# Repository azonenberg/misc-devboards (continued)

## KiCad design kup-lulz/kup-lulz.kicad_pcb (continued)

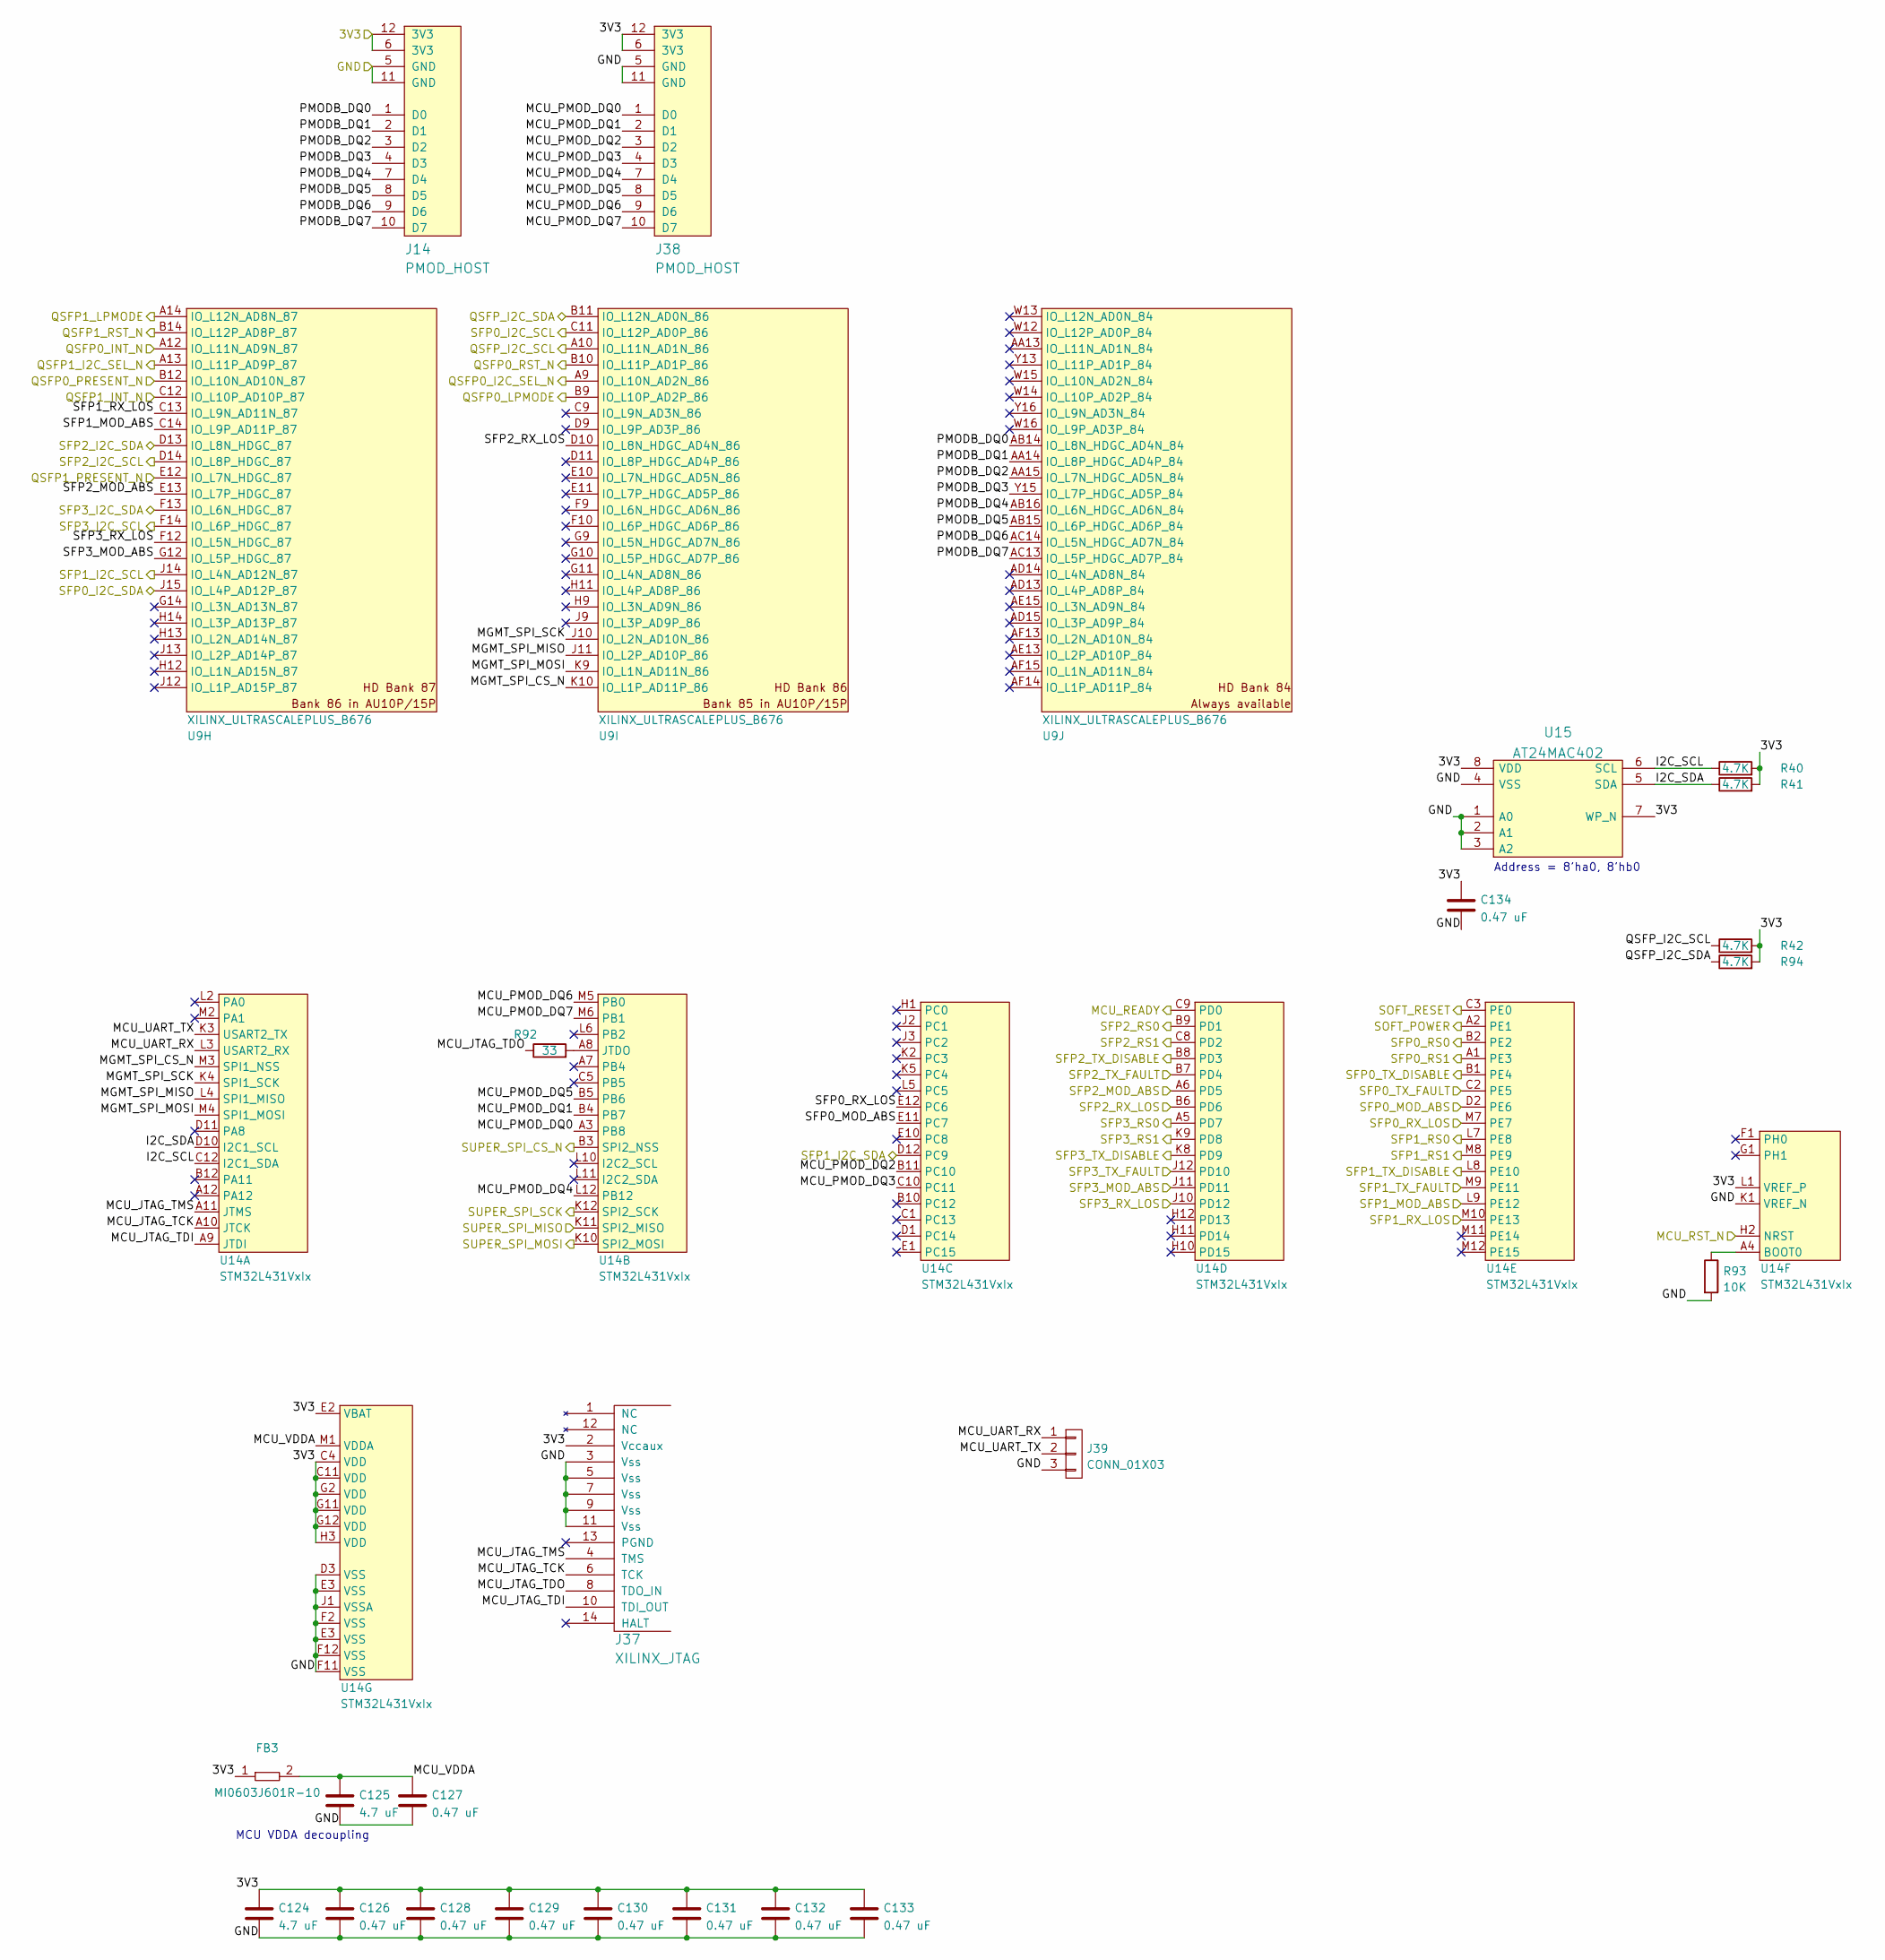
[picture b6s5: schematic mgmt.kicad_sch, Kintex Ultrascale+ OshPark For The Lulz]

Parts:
C124, C125: 4.7 uF; EIA_0603_CAP_NOSILK
C126, C127, C128, C129, C130, C131, C132, C133, C134: 0.47 uF; EIA_0402_CAP_NOSILK
FB3: MI0603J601R-10; EIA_0603_INDUCTOR_NOSILK
J14, J38: PMOD_HOST; CONN_HEADER_2.54MM_2x6_RA_PMOD_HOST
J37: XILINX_JTAG; XILINX_JTAG_PTH_MOLEX_0878311420
J39: CONN_01X03; CONN_HEADER_2.54MM_1x3
R40, R41, R42, R94: 4.7K; EIA_0402_RES_NOSILK
R92: 33; EIA_0402_RES_NOSILK
R93: 10K; EIA_0402_RES_NOSILK
U9: XILINX_ULTRASCALEPLUS_B676; BGA_676_27x27_FULLARRAY_1MM_FFG676
U14: STM32L431VxIx; BGA_100_7x7_DEPOP_0.5MM_STM32_UFBGA100_OSHPARK
U15: AT24MAC402; DFN_8_0.5MM_2x3MM_TALL

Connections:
/3V3: C124.1, C126.1, C128.1, C129.1, C130.1, C131.1, C132.1, C133.1, C134.1, FB3.1, J14.6 (3V3), J14.12 (3V3), J37.2 (Vccaux), J38.6 (3V3), J38.12 (3V3), R40.2, R41.2, R42.2, R94.2, U14.C4 (VDD), U14.C11 (VDD), U14.E2 (VBAT), U14.G2 (VDD), U14.G11 (VDD), U14.G12 (VDD), U14.H3 (VDD), U14.L1 (VREF_P), U15.7 (WP_N), U15.8 (VDD); also elsewhere on the board
/GND: C124.2, C125.2, C126.2, C127.2, C128.2, C129.2, C130.2, C131.2, C132.2, C133.2, C134.2, J14.5 (GND), J14.11 (GND), J37.3 (Vss), J37.5 (Vss), J37.7 (Vss), J37.9 (Vss), J37.11 (Vss), J38.5 (GND), J38.11 (GND), J39.3, R93.2, U14.D3 (VSS), U14.E3 (VSS), U14.F2 (VSS), U14.F11 (VSS), U14.F12 (VSS), U14.J1 (VSSA), U14.K1 (VREF_N), U15.1 (A0), U15.2 (A1), U15.3 (A2), U15.4 (VSS); also elsewhere on the board
/Management/I2C_SCL: R40.1, U14.C12 (I2C1_SDA), U15.6 (SCL)
/Management/I2C_SDA: R41.1, U14.D10 (I2C1_SCL), U15.5 (SDA)
/Management/MCU_JTAG_TCK: J37.6 (TCK), U14.A10 (JTCK)
/Management/MCU_JTAG_TDI: J37.10 (TDI_OUT), U14.A9 (JTDI)
/Management/MCU_JTAG_TDO: J37.8 (TDO_IN), R92.1
/Management/MCU_JTAG_TMS: J37.4 (TMS), U14.A11 (JTMS)
/Management/MCU_PMOD_DQ0: J38.1 (D0), U14.A3 (PB8)
/Management/MCU_PMOD_DQ1: J38.2 (D1), U14.B4 (PB7)
/Management/MCU_PMOD_DQ2: J38.3 (D2), U14.B11 (PC10)
/Management/MCU_PMOD_DQ3: J38.4 (D3), U14.C10 (PC11)
/Management/MCU_PMOD_DQ4: J38.7 (D4), U14.L12 (PB12)
/Management/MCU_PMOD_DQ5: J38.8 (D5), U14.B5 (PB6)
/Management/MCU_PMOD_DQ6: J38.9 (D6), U14.M5 (PB0)
/Management/MCU_PMOD_DQ7: J38.10 (D7), U14.M6 (PB1)
/Management/MCU_READY: U14.C9 (PD0); also elsewhere on the board
/Management/MCU_RST_N: U14.H2 (NRST); also elsewhere on the board
/Management/MCU_UART_RX: J39.1, U14.L3 (USART2_RX)
/Management/MCU_UART_TX: J39.2, U14.K3 (USART2_TX)
/Management/MCU_VDDA: C125.1, C127.1, FB3.2, U14.M1 (VDDA)
/Management/MGMT_SPI_CS_N: U9.K10 (IO_L1P_AD11P_86), U14.M3 (SPI1_NSS)
/Management/MGMT_SPI_MISO: U9.J11 (IO_L2P_AD10P_86), U14.L4 (SPI1_MISO)
/Management/MGMT_SPI_MOSI: U9.K9 (IO_L1N_AD11N_86), U14.M4 (SPI1_MOSI)
/Management/MGMT_SPI_SCK: U9.J10 (IO_L2N_AD10N_86), U14.K4 (SPI1_SCK)
/Management/PMODB_DQ0: J14.1 (D0), U9.AB14 (IO_L8N_HDGC_AD4N_84)
/Management/PMODB_DQ1: J14.2 (D1), U9.AA14 (IO_L8P_HDGC_AD4P_84)
/Management/PMODB_DQ2: J14.3 (D2), U9.AA15 (IO_L7N_HDGC_AD5N_84)
/Management/PMODB_DQ3: J14.4 (D3), U9.Y15 (IO_L7P_HDGC_AD5P_84)
/Management/PMODB_DQ4: J14.7 (D4), U9.AB16 (IO_L6N_HDGC_AD6N_84)
/Management/PMODB_DQ5: J14.8 (D5), U9.AB15 (IO_L6P_HDGC_AD6P_84)
/Management/PMODB_DQ6: J14.9 (D6), U9.AC14 (IO_L5N_HDGC_AD7N_84)
/Management/PMODB_DQ7: J14.10 (D7), U9.AC13 (IO_L5P_HDGC_AD7P_84)
/Management/QSFP0_I2C_SEL_N: U9.A9 (IO_L10N_AD2N_86); also elsewhere on the board
/Management/QSFP0_INT_N: U9.A12 (IO_L11N_AD9N_87); also elsewhere on the board
/Management/QSFP0_LPMODE: U9.B9 (IO_L10P_AD2P_86); also elsewhere on the board
/Management/QSFP0_PRESENT_N: U9.B12 (IO_L10N_AD10N_87); also elsewhere on the board
/Management/QSFP0_RST_N: U9.B10 (IO_L11P_AD1P_86); also elsewhere on the board
/Management/QSFP1_I2C_SEL_N: U9.A13 (IO_L11P_AD9P_87); also elsewhere on the board
/Management/QSFP1_INT_N: U9.C12 (IO_L10P_AD10P_87); also elsewhere on the board
/Management/QSFP1_LPMODE: U9.A14 (IO_L12N_AD8N_87); also elsewhere on the board
/Management/QSFP1_PRESENT_N: U9.E12 (IO_L7N_HDGC_87); also elsewhere on the board
/Management/QSFP1_RST_N: U9.B14 (IO_L12P_AD8P_87); also elsewhere on the board
/Management/QSFP_I2C_SCL: R42.1, U9.A10 (IO_L11N_AD1N_86); also elsewhere on the board
/Management/QSFP_I2C_SDA: R94.1, U9.B11 (IO_L12N_AD0N_86); also elsewhere on the board
/Management/SFP0_MOD_ABS: U14.D2 (PE6), U14.E11 (PC7); also elsewhere on the board
/Management/SFP0_RS0: U14.B2 (PE2); also elsewhere on the board
/Management/SFP0_RS1: U14.A1 (PE3); also elsewhere on the board
/Management/SFP0_RX_LOS: U14.E12 (PC6), U14.M7 (PE7); also elsewhere on the board
/Management/SFP0_TX_DISABLE: U14.B1 (PE4); also elsewhere on the board
/Management/SFP0_TX_FAULT: U14.C2 (PE5); also elsewhere on the board
/Management/SFP1_MOD_ABS: U9.C14 (IO_L9P_AD11P_87), U14.L9 (PE12); also elsewhere on the board
/Management/SFP1_RS0: U14.L7 (PE8); also elsewhere on the board
/Management/SFP1_RS1: U14.M8 (PE9); also elsewhere on the board
/Management/SFP1_RX_LOS: U9.C13 (IO_L9N_AD11N_87), U14.M10 (PE13); also elsewhere on the board
/Management/SFP1_TX_DISABLE: U14.L8 (PE10); also elsewhere on the board
/Management/SFP1_TX_FAULT: U14.M9 (PE11); also elsewhere on the board
/Management/SFP2_MOD_ABS: U9.E13 (IO_L7P_HDGC_87), U14.A6 (PD5); also elsewhere on the board
/Management/SFP2_RS0: U14.B9 (PD1); also elsewhere on the board
/Management/SFP2_RS1: U14.C8 (PD2); also elsewhere on the board
/Management/SFP2_RX_LOS: U9.D10 (IO_L8N_HDGC_AD4N_86), U14.B6 (PD6); also elsewhere on the board
/Management/SFP2_TX_DISABLE: U14.B8 (PD3); also elsewhere on the board
/Management/SFP2_TX_FAULT: U14.B7 (PD4); also elsewhere on the board
/Management/SFP3_MOD_ABS: U9.G12 (IO_L5P_HDGC_87), U14.J11 (PD11); also elsewhere on the board
/Management/SFP3_RS0: U14.A5 (PD7); also elsewhere on the board
/Management/SFP3_RS1: U14.K9 (PD8); also elsewhere on the board
/Management/SFP3_RX_LOS: U9.F12 (IO_L5N_HDGC_87), U14.J10 (PD12); also elsewhere on the board
/Management/SFP3_TX_DISABLE: U14.K8 (PD9); also elsewhere on the board
/Management/SFP3_TX_FAULT: U14.J12 (PD10); also elsewhere on the board
/Power Supply/SOFT_POWER: U14.A2 (PE1); also elsewhere on the board
/Power Supply/SOFT_RESET: U14.C3 (PE0); also elsewhere on the board
/Power Supply/SUPER_SPI_CS_N: U14.B3 (SPI2_NSS); also elsewhere on the board
/Power Supply/SUPER_SPI_MISO: U14.K11 (SPI2_MISO); also elsewhere on the board
/Power Supply/SUPER_SPI_MOSI: U14.K10 (SPI2_MOSI); also elsewhere on the board
/Power Supply/SUPER_SPI_SCK: U14.K12 (SPI2_SCK); also elsewhere on the board
/SFP28 interfaces/SFP0_I2C_SCL: U9.C11 (IO_L12P_AD0P_86); also elsewhere on the board
/SFP28 interfaces/SFP0_I2C_SDA: U9.J15 (IO_L4P_AD12P_87); also elsewhere on the board
/SFP28 interfaces/SFP1_I2C_SCL: U9.J14 (IO_L4N_AD12N_87); also elsewhere on the board
/SFP28 interfaces/SFP1_I2C_SDA: U14.D12 (PC9); also elsewhere on the board
/SFP28 interfaces/SFP2_I2C_SCL: U9.D14 (IO_L8P_HDGC_87); also elsewhere on the board
/SFP28 interfaces/SFP2_I2C_SDA: U9.D13 (IO_L8N_HDGC_87); also elsewhere on the board
/SFP28 interfaces/SFP3_I2C_SCL: U9.F14 (IO_L6P_HDGC_87); also elsewhere on the board
/SFP28 interfaces/SFP3_I2C_SDA: U9.F13 (IO_L6N_HDGC_87); also elsewhere on the board
unnamed: R92.2, U14.A8 (JTDO)
unnamed: R93.1, U14.A4 (BOOT0)

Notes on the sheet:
Address = 8'ha0, 8'hb0
MCU VDDA decoupling

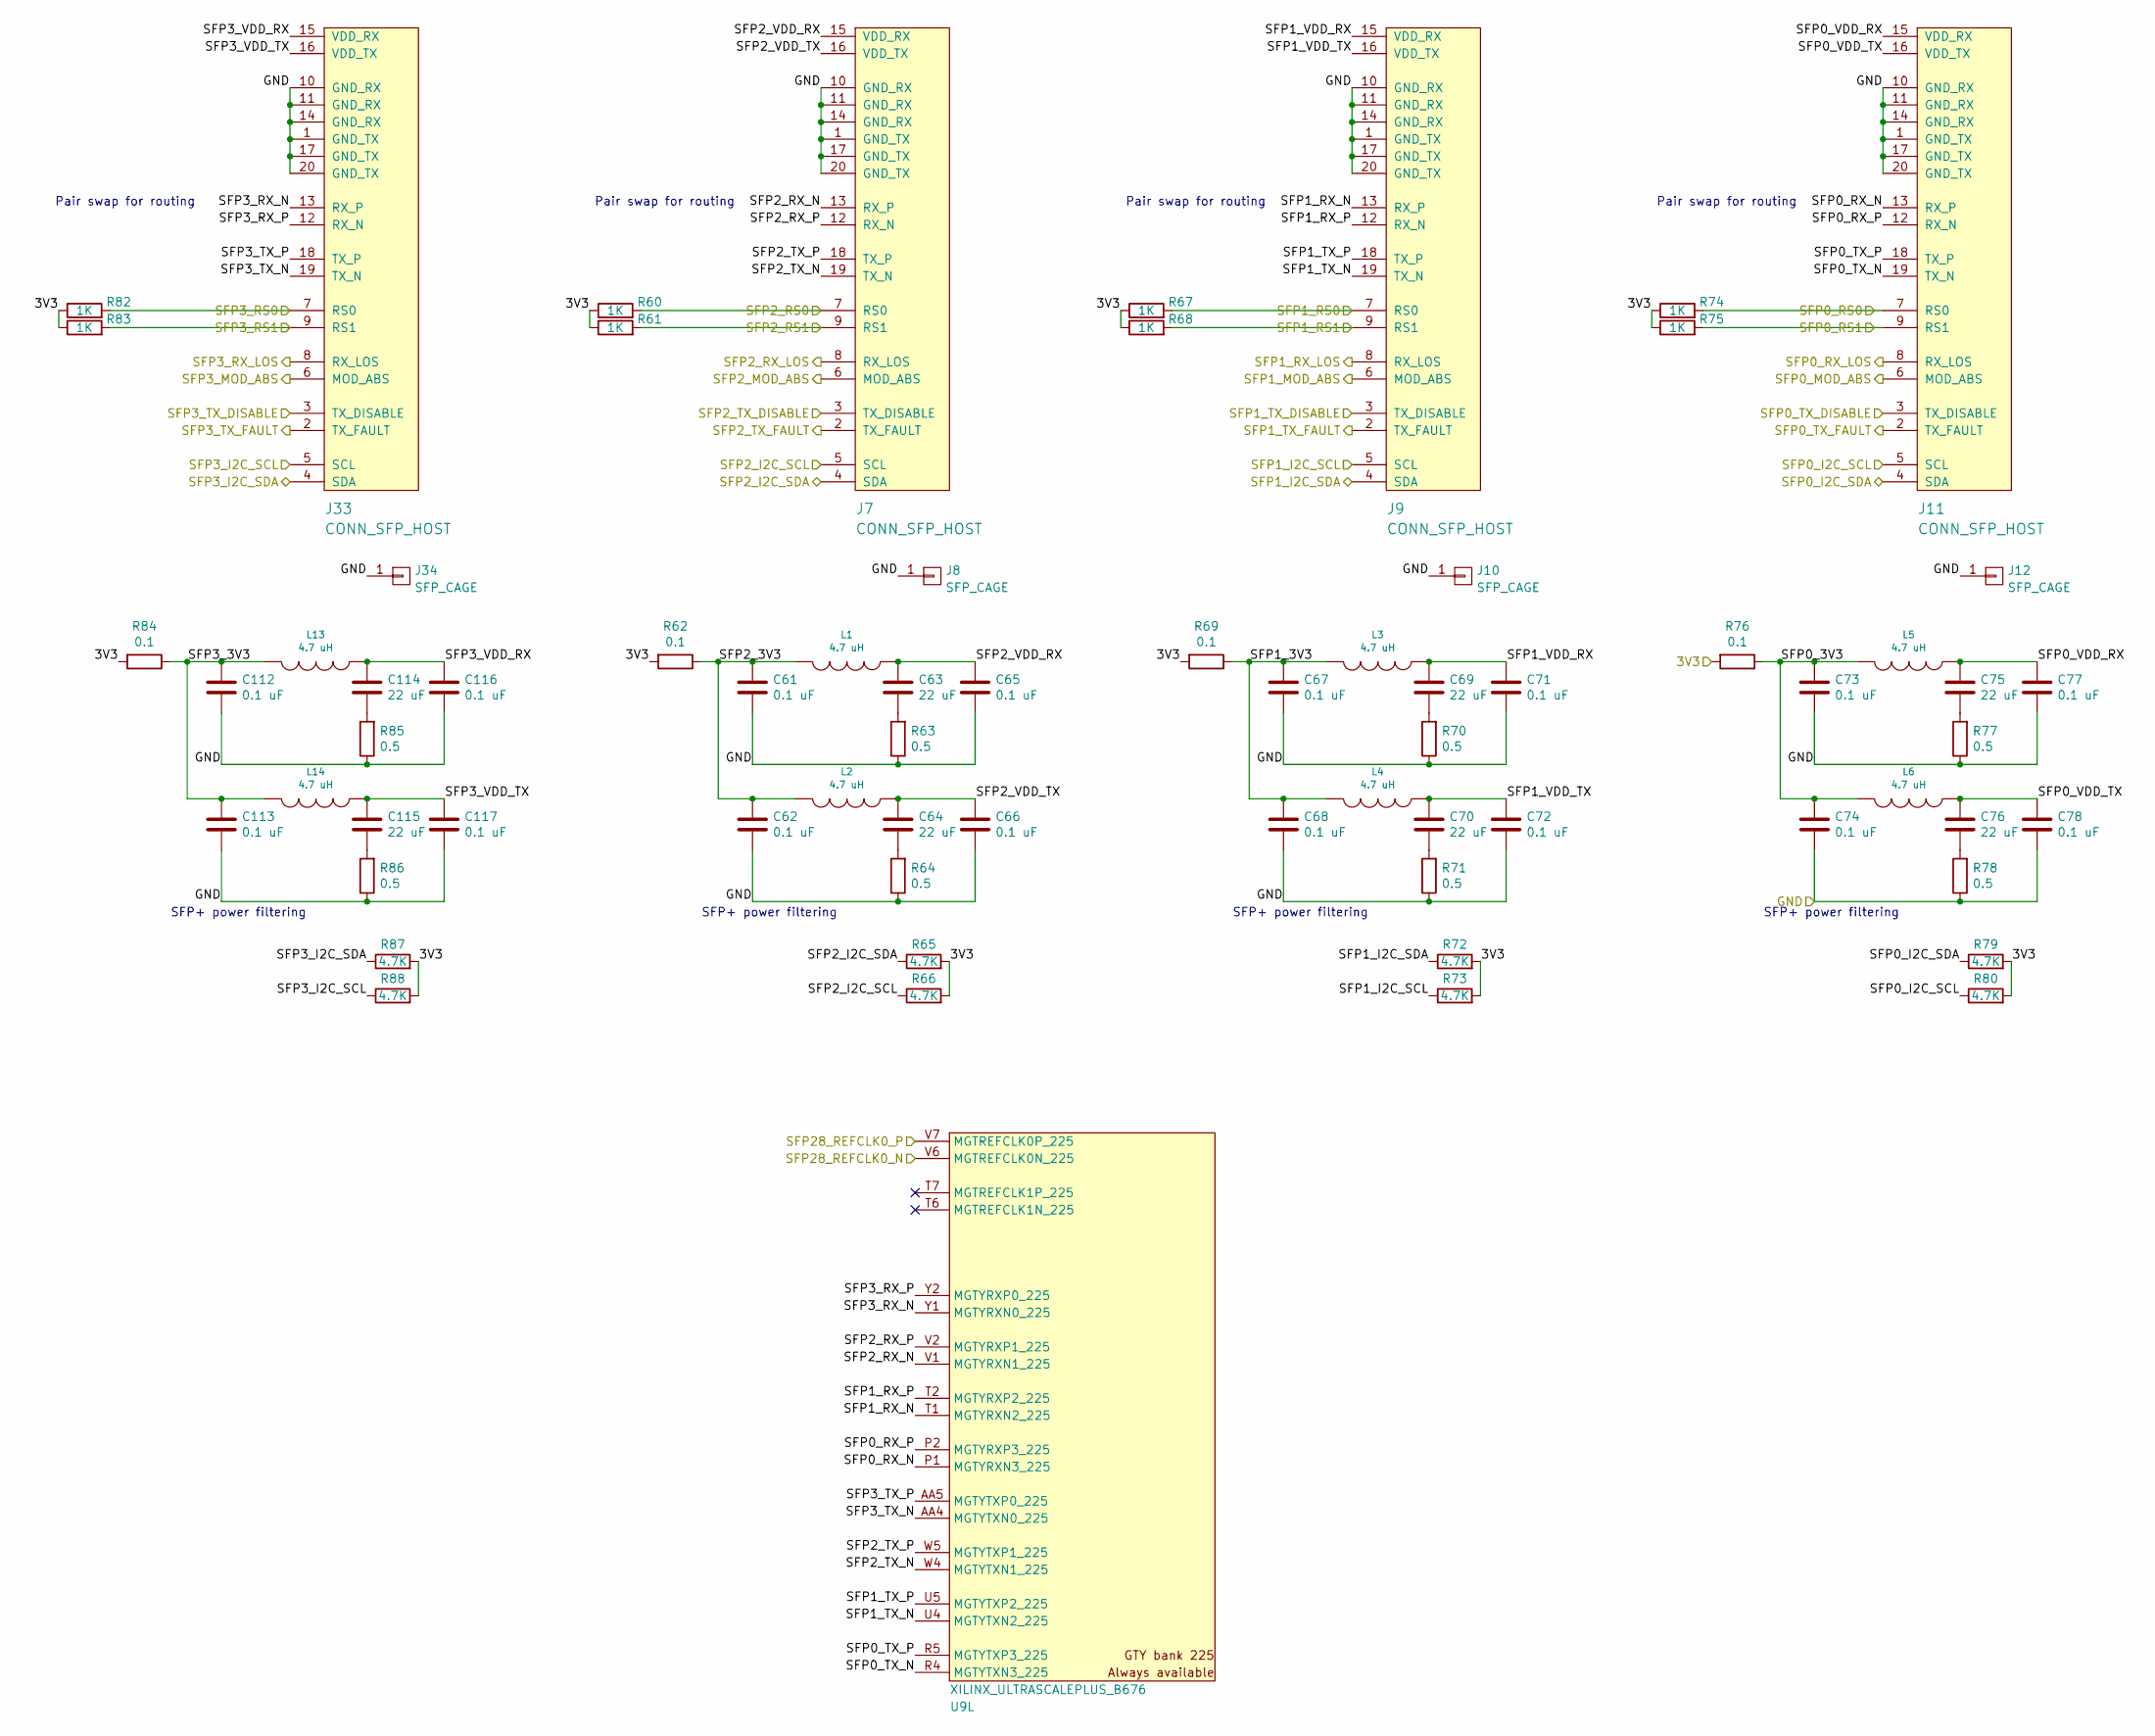
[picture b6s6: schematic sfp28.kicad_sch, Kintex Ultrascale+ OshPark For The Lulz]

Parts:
C61, C62, C65, C66, C67, C68, C71, C72, C73, C74, C77, C78, C112, C113, C116, C117: 0.1 uF; EIA_0402_CAP_NOSILK
C63, C64, C69, C70, C75, C76, C114, C115: 22 uF; EIA_0805_CAP_NOSILK
J7, J9, J11, J33: CONN_SFP_HOST; CONN_SFP+_AMPHENOL_UE76_A10_2000T
J8, J10, J12, J34: SFP_CAGE; CONN_SFP_CAGE_TE_2007194-1
L1, L2, L3, L4, L5, L6, L13, L14: 4.7 uH; EIA_0805_INDUCTOR_NOSILK
R60, R61, R67, R68, R74, R75, R82, R83: 1K; EIA_0402_RES_NOSILK
R62, R69, R76, R84: 0.1; EIA_0402_RES_NOSILK
R63, R64, R70, R71, R77, R78, R85, R86: 0.5; EIA_0402_RES_NOSILK
R65, R66, R72, R73, R79, R80, R87, R88: 4.7K; EIA_0402_RES_NOSILK
U9: XILINX_ULTRASCALEPLUS_B676; BGA_676_27x27_FULLARRAY_1MM_FFG676

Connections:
/3V3: R60.1, R61.1, R62.2, R65.2, R66.2, R67.1, R68.1, R69.2, R72.2, R73.2, R74.1, R75.1, R76.2, R79.2, R80.2, R82.1, R83.1, R84.2, R87.2, R88.2; also elsewhere on the board
/GND: C61.2, C62.2, C65.2, C66.2, C67.2, C68.2, C71.2, C72.2, C73.2, C74.2, C77.2, C78.2, C112.2, C113.2, C116.2, C117.2, J7.1 (GND_TX), J7.10 (GND_RX), J7.11 (GND_RX), J7.14 (GND_RX), J7.17 (GND_TX), J7.20 (GND_TX), J8.1, J9.1 (GND_TX), J9.10 (GND_RX), J9.11 (GND_RX), J9.14 (GND_RX), J9.17 (GND_TX), J9.20 (GND_TX), J10.1, J11.1 (GND_TX), J11.10 (GND_RX), J11.11 (GND_RX), J11.14 (GND_RX), J11.17 (GND_TX), J11.20 (GND_TX), J12.1, J33.1 (GND_TX), J33.10 (GND_RX), J33.11 (GND_RX), J33.14 (GND_RX), J33.17 (GND_TX), J33.20 (GND_TX), J34.1, R63.1, R64.1, R70.1, R71.1, R77.1, R78.1, R85.1, R86.1; also elsewhere on the board
/Management/SFP0_MOD_ABS: J11.6 (MOD_ABS); also elsewhere on the board
/Management/SFP0_RS0: J11.7 (RS0), R74.2; also elsewhere on the board
/Management/SFP0_RS1: J11.9 (RS1), R75.2; also elsewhere on the board
/Management/SFP0_RX_LOS: J11.8 (RX_LOS); also elsewhere on the board
/Management/SFP0_TX_DISABLE: J11.3 (TX_DISABLE); also elsewhere on the board
/Management/SFP0_TX_FAULT: J11.2 (TX_FAULT); also elsewhere on the board
/Management/SFP1_MOD_ABS: J9.6 (MOD_ABS); also elsewhere on the board
/Management/SFP1_RS0: J9.7 (RS0), R67.2; also elsewhere on the board
/Management/SFP1_RS1: J9.9 (RS1), R68.2; also elsewhere on the board
/Management/SFP1_RX_LOS: J9.8 (RX_LOS); also elsewhere on the board
/Management/SFP1_TX_DISABLE: J9.3 (TX_DISABLE); also elsewhere on the board
/Management/SFP1_TX_FAULT: J9.2 (TX_FAULT); also elsewhere on the board
/Management/SFP2_MOD_ABS: J7.6 (MOD_ABS); also elsewhere on the board
/Management/SFP2_RS0: J7.7 (RS0), R60.2; also elsewhere on the board
/Management/SFP2_RS1: J7.9 (RS1), R61.2; also elsewhere on the board
/Management/SFP2_RX_LOS: J7.8 (RX_LOS); also elsewhere on the board
/Management/SFP2_TX_DISABLE: J7.3 (TX_DISABLE); also elsewhere on the board
/Management/SFP2_TX_FAULT: J7.2 (TX_FAULT); also elsewhere on the board
/Management/SFP3_MOD_ABS: J33.6 (MOD_ABS); also elsewhere on the board
/Management/SFP3_RS0: J33.7 (RS0), R82.2; also elsewhere on the board
/Management/SFP3_RS1: J33.9 (RS1), R83.2; also elsewhere on the board
/Management/SFP3_RX_LOS: J33.8 (RX_LOS); also elsewhere on the board
/Management/SFP3_TX_DISABLE: J33.3 (TX_DISABLE); also elsewhere on the board
/Management/SFP3_TX_FAULT: J33.2 (TX_FAULT); also elsewhere on the board
/REFCLK1_N: U9.V6 (MGTREFCLK0N_225); also elsewhere on the board
/REFCLK1_P: U9.V7 (MGTREFCLK0P_225); also elsewhere on the board
/SFP28 interfaces/SFP0_3V3: C73.1, C74.1, L5.2, L6.2, R76.1
/SFP28 interfaces/SFP0_I2C_SCL: J11.5 (SCL), R80.1; also elsewhere on the board
/SFP28 interfaces/SFP0_I2C_SDA: J11.4 (SDA), R79.1; also elsewhere on the board
/SFP28 interfaces/SFP0_RX_N: J11.13 (RX_P), U9.P1 (MGTYRXN3_225)
/SFP28 interfaces/SFP0_RX_P: J11.12 (RX_N), U9.P2 (MGTYRXP3_225)
/SFP28 interfaces/SFP0_TX_N: J11.19 (TX_N), U9.R4 (MGTYTXN3_225)
/SFP28 interfaces/SFP0_TX_P: J11.18 (TX_P), U9.R5 (MGTYTXP3_225)
/SFP28 interfaces/SFP0_VDD_RX: C75.1, C77.1, J11.15 (VDD_RX), L5.1
/SFP28 interfaces/SFP0_VDD_TX: C76.1, C78.1, J11.16 (VDD_TX), L6.1
/SFP28 interfaces/SFP1_3V3: C67.1, C68.1, L3.2, L4.2, R69.1
/SFP28 interfaces/SFP1_I2C_SCL: J9.5 (SCL), R73.1; also elsewhere on the board
/SFP28 interfaces/SFP1_I2C_SDA: J9.4 (SDA), R72.1; also elsewhere on the board
/SFP28 interfaces/SFP1_RX_N: J9.13 (RX_P), U9.T1 (MGTYRXN2_225)
/SFP28 interfaces/SFP1_RX_P: J9.12 (RX_N), U9.T2 (MGTYRXP2_225)
/SFP28 interfaces/SFP1_TX_N: J9.19 (TX_N), U9.U4 (MGTYTXN2_225)
/SFP28 interfaces/SFP1_TX_P: J9.18 (TX_P), U9.U5 (MGTYTXP2_225)
/SFP28 interfaces/SFP1_VDD_RX: C69.1, C71.1, J9.15 (VDD_RX), L3.1
/SFP28 interfaces/SFP1_VDD_TX: C70.1, C72.1, J9.16 (VDD_TX), L4.1
/SFP28 interfaces/SFP2_3V3: C61.1, C62.1, L1.2, L2.2, R62.1
/SFP28 interfaces/SFP2_I2C_SCL: J7.5 (SCL), R66.1; also elsewhere on the board
/SFP28 interfaces/SFP2_I2C_SDA: J7.4 (SDA), R65.1; also elsewhere on the board
/SFP28 interfaces/SFP2_RX_N: J7.13 (RX_P), U9.V1 (MGTYRXN1_225)
/SFP28 interfaces/SFP2_RX_P: J7.12 (RX_N), U9.V2 (MGTYRXP1_225)
/SFP28 interfaces/SFP2_TX_N: J7.19 (TX_N), U9.W4 (MGTYTXN1_225)
/SFP28 interfaces/SFP2_TX_P: J7.18 (TX_P), U9.W5 (MGTYTXP1_225)
/SFP28 interfaces/SFP2_VDD_RX: C63.1, C65.1, J7.15 (VDD_RX), L1.1
/SFP28 interfaces/SFP2_VDD_TX: C64.1, C66.1, J7.16 (VDD_TX), L2.1
/SFP28 interfaces/SFP3_3V3: C112.1, C113.1, L13.2, L14.2, R84.1
/SFP28 interfaces/SFP3_I2C_SCL: J33.5 (SCL), R88.1; also elsewhere on the board
/SFP28 interfaces/SFP3_I2C_SDA: J33.4 (SDA), R87.1; also elsewhere on the board
/SFP28 interfaces/SFP3_RX_N: J33.13 (RX_P), U9.Y1 (MGTYRXN0_225)
/SFP28 interfaces/SFP3_RX_P: J33.12 (RX_N), U9.Y2 (MGTYRXP0_225)
/SFP28 interfaces/SFP3_TX_N: J33.19 (TX_N), U9.AA4 (MGTYTXN0_225)
/SFP28 interfaces/SFP3_TX_P: J33.18 (TX_P), U9.AA5 (MGTYTXP0_225)
/SFP28 interfaces/SFP3_VDD_RX: C114.1, C116.1, J33.15 (VDD_RX), L13.1
/SFP28 interfaces/SFP3_VDD_TX: C115.1, C117.1, J33.16 (VDD_TX), L14.1
unnamed: C63.2, R63.2
unnamed: C64.2, R64.2
unnamed: C69.2, R70.2
unnamed: C70.2, R71.2
unnamed: C75.2, R77.2
unnamed: C76.2, R78.2
unnamed: C114.2, R85.2
unnamed: C115.2, R86.2

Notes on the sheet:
Pair swap for routing
SFP+ power filtering

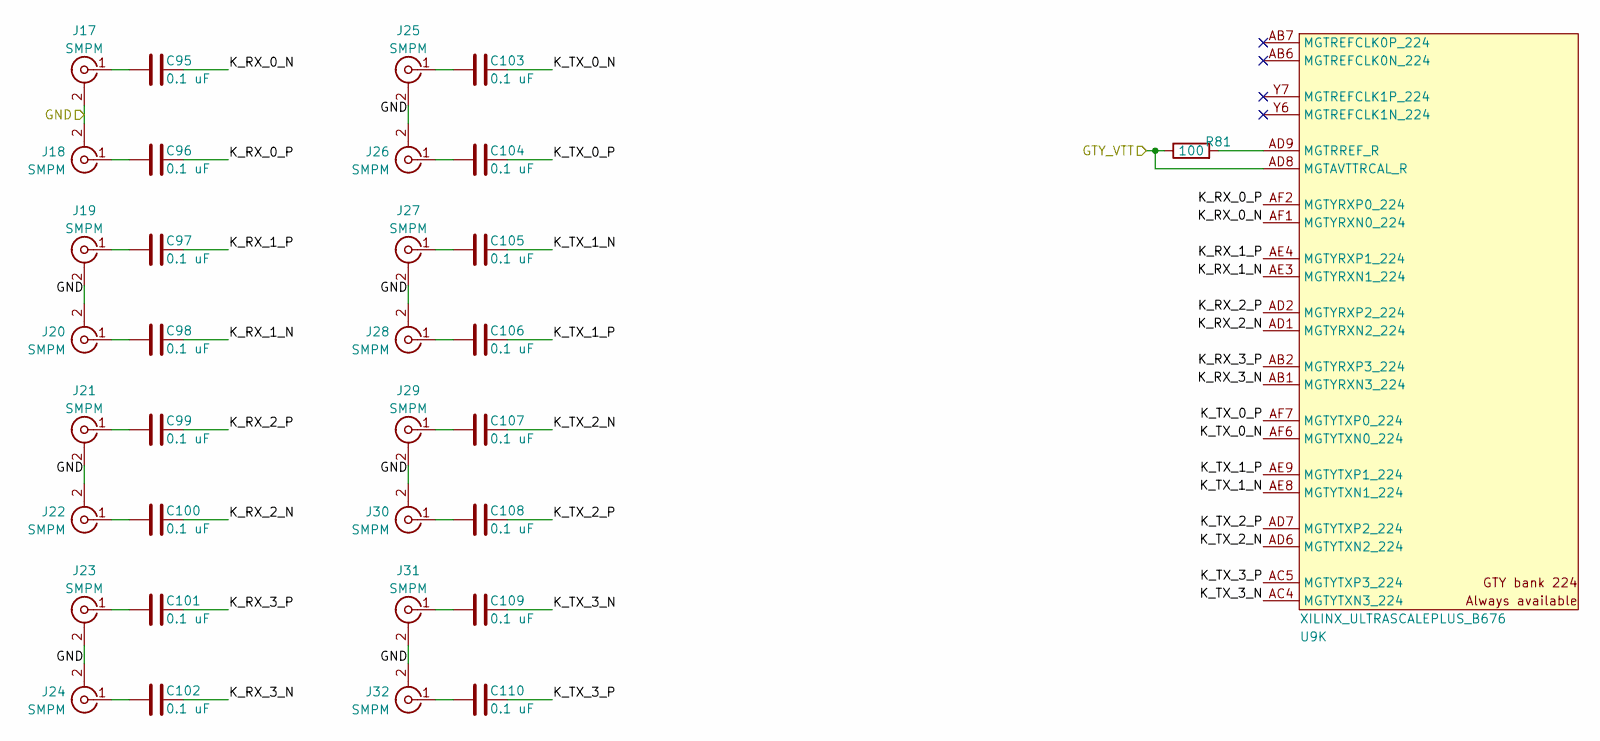
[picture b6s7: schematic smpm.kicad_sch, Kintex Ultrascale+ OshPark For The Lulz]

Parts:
C95, C96, C97, C98, C99, C100, C101, C102, C103, C104, C105, C106, C107, C108, C109, C110: 0.1 uF; EIA_0402_CAP_NOSILK
J17, J18, J19, J20, J21, J22, J23, J24, J25, J26, J27, J28, J29, J30, J31, J32: SMPM; CONN_SMPM_AMPHENOL_C925-197J-51PT
R81: 100; EIA_0402_RES_NOSILK
U9: XILINX_ULTRASCALEPLUS_B676; BGA_676_27x27_FULLARRAY_1MM_FFG676

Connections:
/GND: J17.2 (Ext), J18.2 (Ext), J19.2 (Ext), J20.2 (Ext), J21.2 (Ext), J22.2 (Ext), J23.2 (Ext), J24.2 (Ext), J25.2 (Ext), J26.2 (Ext), J27.2 (Ext), J28.2 (Ext), J29.2 (Ext), J30.2 (Ext), J31.2 (Ext), J32.2 (Ext); also elsewhere on the board
/GTY_VTT: R81.1, U9.AD8 (MGTAVTTRCAL_R); also elsewhere on the board
/SMPM ports/K_RX_0_N: C95.2, U9.AF1 (MGTYRXN0_224)
/SMPM ports/K_RX_0_P: C96.2, U9.AF2 (MGTYRXP0_224)
/SMPM ports/K_RX_1_N: C98.2, U9.AE3 (MGTYRXN1_224)
/SMPM ports/K_RX_1_P: C97.2, U9.AE4 (MGTYRXP1_224)
/SMPM ports/K_RX_2_N: C100.2, U9.AD1 (MGTYRXN2_224)
/SMPM ports/K_RX_2_P: C99.2, U9.AD2 (MGTYRXP2_224)
/SMPM ports/K_RX_3_N: C102.2, U9.AB1 (MGTYRXN3_224)
/SMPM ports/K_RX_3_P: C101.2, U9.AB2 (MGTYRXP3_224)
/SMPM ports/K_TX_0_N: C103.2, U9.AF6 (MGTYTXN0_224)
/SMPM ports/K_TX_0_P: C104.2, U9.AF7 (MGTYTXP0_224)
/SMPM ports/K_TX_1_N: C105.2, U9.AE8 (MGTYTXN1_224)
/SMPM ports/K_TX_1_P: C106.2, U9.AE9 (MGTYTXP1_224)
/SMPM ports/K_TX_2_N: C107.2, U9.AD6 (MGTYTXN2_224)
/SMPM ports/K_TX_2_P: C108.2, U9.AD7 (MGTYTXP2_224)
/SMPM ports/K_TX_3_N: C109.2, U9.AC4 (MGTYTXN3_224)
/SMPM ports/K_TX_3_P: C110.2, U9.AC5 (MGTYTXP3_224)
unnamed: C95.1, J17.1 (In)
unnamed: C96.1, J18.1 (In)
unnamed: C97.1, J19.1 (In)
unnamed: C98.1, J20.1 (In)
unnamed: C99.1, J21.1 (In)
unnamed: C100.1, J22.1 (In)
unnamed: C101.1, J23.1 (In)
unnamed: C102.1, J24.1 (In)
unnamed: C103.1, J25.1 (In)
unnamed: C104.1, J26.1 (In)
unnamed: C105.1, J27.1 (In)
unnamed: C106.1, J28.1 (In)
unnamed: C107.1, J29.1 (In)
unnamed: C108.1, J30.1 (In)
unnamed: C109.1, J31.1 (In)
unnamed: C110.1, J32.1 (In)
unnamed: R81.2, U9.AD9 (MGTRREF_R)
